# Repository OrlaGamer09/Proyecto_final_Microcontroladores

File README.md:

# Final Project Microcontrollers  
- [Spanish](./README_es.md) 

> **IMPORTANT**: This project was born from the idea of creating a Christmas-themed box, equipped with electronics, as part of the final project for the Microcontrollers course (November 2024).  

## Project Description  
The project consists of an interactive Christmas box, controlled by a **PIC16F877A** microcontroller, designed to combine creativity, electronics, and programming into a single functional device.  

## Roles and Tools Used  

### Roles  
The team is composed of:  
- **Orlando Arroyo**  
- **María López**  
- **Andrés Fábregas**  

All members participated in various roles, including:  
- Software and hardware development.  
- Product management.  

### Tools  
- **Notion**: For task assignment and progress tracking.  
- **MPLAB X IDE v5.35** and **XC8 v2.5**: For microcontroller programming.  
- **Autodesk EAGLE**: For schematic and PCB design.  

## System Operation  

Once powered on, the system displays an **initial Christmas message** on the LCD screen. From this point, the LDR sensor evaluates light conditions to determine if it is day or night, activating one of the following modes:  

### **Night Mode**  
- A decorative light is turned on.  
- A themed message is displayed on the LCD screen.  

### **Day Mode**  
In this mode, the system uses an ultrasonic sensor to detect the proximity of an object or person. If presence is detected, the following functions are activated:  
1. **Stepper motor**: Rotates a decorative figure.  
2. **Speaker**: Plays a Christmas melody.  
3. **LED strip**: Blinks in sync with the music using PWM.  
4. **LCD screen**: Displays a message related to the current activity.  

## PIC16F877A Resource Allocation  

The system utilizes the resources of the **PIC16F877A** microcontroller as follows:  

- **Port D**: Controls the LCD screen (RD0 to RD5 as outputs).  
- **Port B**: Controls the stepper motor (RB0 to RB3 as outputs).  
- **Port A**: Manages the sensors:  
  - **RA0**: Analog input for the LDR sensor.  
  - **RA1 and RA2**: Controls the ultrasonic sensor:  
    - **RA1 (Trigger)**: Output.  
    - **RA2 (Echo)**: Input.  
- **Port C**: Controls the speaker and LED strip.

## Schematic and PCB Design  

Using **Autodesk EAGLE**, we designed both the schematic and the system's PCB. These designs can be viewed in the images available in the `img` folder:  
- **Schematic**:   
- **PCB**: 

## Final Circuit of the System  

After soldering all the components onto the PCB, this is the final result of the circuit, assembled inside the box:  
- **PCB Circuit**:   

## Final Result  

After decorating the box with a Christmas style, this was the final result of the project:  
- **Photo of the Final Project**:   
- **Functionality Video**: [Watch Video](./img/resultado_final.mp4)

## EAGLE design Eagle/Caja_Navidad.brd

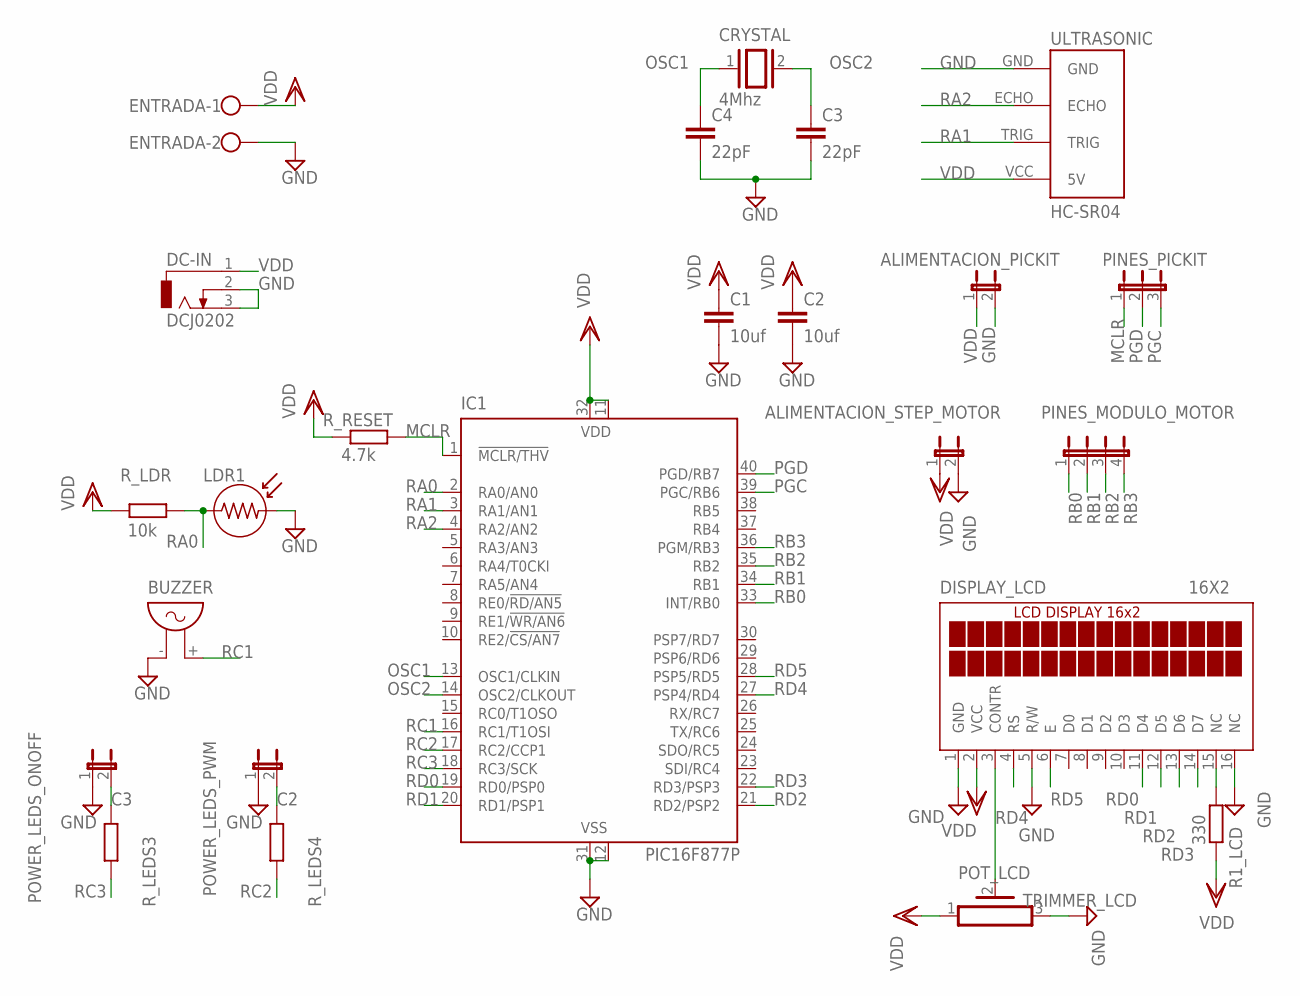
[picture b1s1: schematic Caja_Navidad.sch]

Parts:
ALIMENTACION_PICKIT: JP1E; JP1
ALIMENTACION_STEP_MOTOR: JP1E; JP1
BUZZER: F/QMX
C1, C2: 10uf; C2.5-2
C3, C4: 22pF; C2.5-2
CRYSTAL: 4Mhz; Q
DC-IN: DCJ0202
DISPLAY_LCD: 16X2; TUXGR_16X2_R2
ENTRADA: W237-102
IC1: PIC16F877P; DIL40
LDR1: LDR
PINES_MODULO_MOTOR: JP4E; JP4
PINES_PICKIT: JP2E; JP2
POWER_LEDS_ONOFF: JP1E; JP1
POWER_LEDS_PWM: JP1E; JP1
R1_LCD: 330; 0204/7
R_LDR: 10k; 0204/7
R_LEDS3: 330; 0204/7
R_LEDS4: R-EU_0204/7; 0204/7
R_RESET: 4.7k; 0204/7
TRIMMER_LCD: PV36W
ULTRASONIC: HC-SR04; HC-SR04_FOOTPRINT

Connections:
C2: POWER_LEDS_PWM.2, R_LEDS4.2
C3: POWER_LEDS_ONOFF.2, R_LEDS3.2
GND: ALIMENTACION_PICKIT.2, ALIMENTACION_STEP_MOTOR.2, BUZZER.- (1), C1.2, C2.2, C3.2, C4.2, DC-IN.2, DC-IN.3, DISPLAY_LCD.1 (GND), DISPLAY_LCD.5 (R/W), DISPLAY_LCD.16 (NC), ENTRADA.2, IC1.12 (VSS), IC1.31 (VSS), LDR1.2, POWER_LEDS_ONOFF.1, POWER_LEDS_PWM.1, TRIMMER_LCD.3, ULTRASONIC.GND
MCLR: IC1.1 (!MCLR/THV), PINES_PICKIT.1, R_RESET.2
unnamed: DISPLAY_LCD.15 (NC), R1_LCD.2
OSC1: C4.1, CRYSTAL.1, IC1.13 (OSC1/CLKIN)
OSC2: C3.1, CRYSTAL.2, IC1.14 (OSC2/CLKOUT)
PGC: IC1.39 (PGC/RB6), PINES_PICKIT.3
PGD: IC1.40 (PGD/RB7), PINES_PICKIT.2
POT_LCD: DISPLAY_LCD.3 (CONTR), TRIMMER_LCD.2
RA0: IC1.2 (RA0/AN0), LDR1.1, R_LDR.2
RA1: IC1.3 (RA1/AN1), ULTRASONIC.TRIG
RA2: IC1.4 (RA2/AN2), ULTRASONIC.ECHO
RB0: IC1.33 (INT/RB0), PINES_MODULO_MOTOR.1
RB1: IC1.34 (RB1), PINES_MODULO_MOTOR.2
RB2: IC1.35 (RB2), PINES_MODULO_MOTOR.3
RB3: IC1.36 (PGM/RB3), PINES_MODULO_MOTOR.4
RC1: BUZZER.+ (2), IC1.16 (RC1/T1OSI)
RC2: IC1.17 (RC2/CCP1), R_LEDS4.1
RC3: IC1.18 (RC3/SCK), R_LEDS3.1
RD0: DISPLAY_LCD.11 (D4), IC1.19 (RD0/PSP0)
RD1: DISPLAY_LCD.12 (D5), IC1.20 (RD1/PSP1)
RD2: DISPLAY_LCD.13 (D6), IC1.21 (RD2/PSP2)
RD3: DISPLAY_LCD.14 (D7), IC1.22 (RD3/PSP3)
RD4: DISPLAY_LCD.4 (RS), IC1.27 (PSP4/RD4)
RD5: DISPLAY_LCD.6 (E), IC1.28 (PSP5/RD5)
VDD: ALIMENTACION_PICKIT.1, ALIMENTACION_STEP_MOTOR.1, C1.1, C2.1, DC-IN.1, DISPLAY_LCD.2 (VCC), ENTRADA.1, IC1.11 (VDD), IC1.32 (VDD), R1_LCD.1, R_LDR.1, R_RESET.1, TRIMMER_LCD.1, ULTRASONIC.VCC (5V)

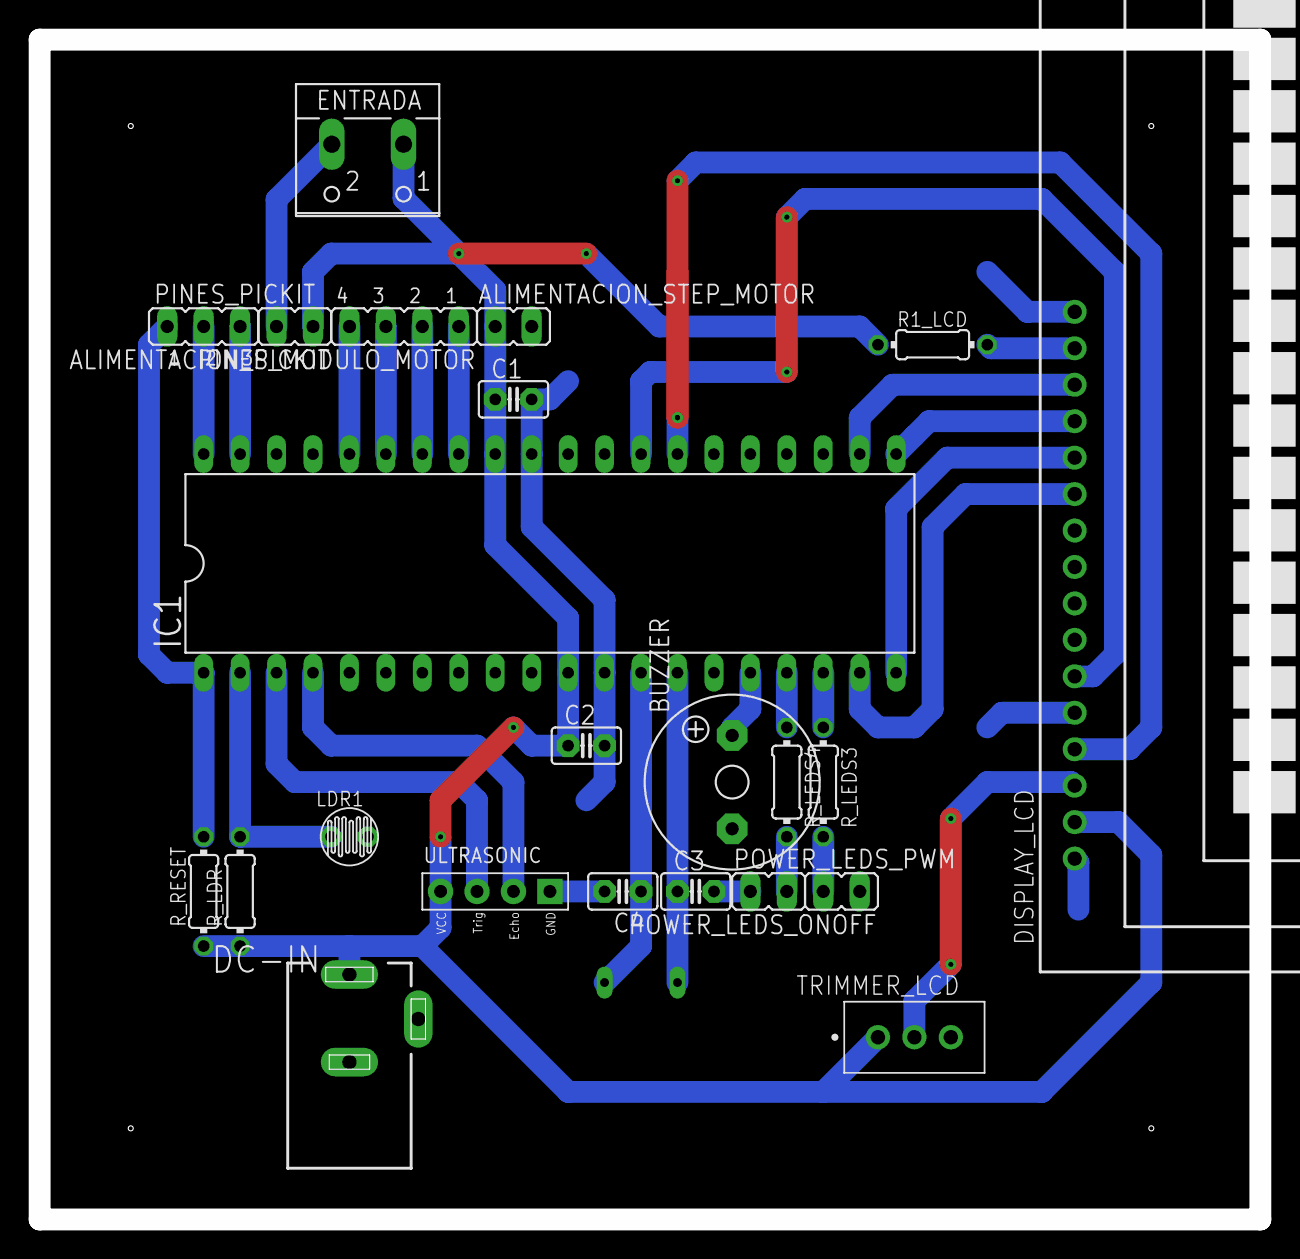
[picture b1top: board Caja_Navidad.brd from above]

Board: 2 copper layers, 85.1 x 82.2 mm, 24 parts (1 on the bottom side), 27 nets.

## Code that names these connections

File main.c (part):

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

// ULTRASONIDO:
#define Trigger RA1 // Pin de Trigger del sensor ultrasónico
#define Echo RA2 // Pin de Echo del sensor ultrasónico
int time_taken;
int distance;
int threshold_distance = 10; // Ajusta el umbral para probar diferentes distancias PULGADAS
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#define shiftLeft    0b00010000 // hace que blink el cursor
#define shiftRight   0b00010100 // hace que blink el cursor
#define lcdPort   PORTD // define el puerto al que se conecta el LCB
#define eBit  PORTDbits.RD5 // define el puerto al que se conecta E
#define rsBit  PORTDbits.RD4 // define el puerto al que se conecta RS
unsigned char lcdInfo, lcdTempInfo, rsOr; // 8 bit location for 3 variables
unsigned char n; // 8 bit location
char str[80]; //80 posiciones de memoria para enviar string a LCD
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void parpadearLEDs(void) {
    CCP1CON = 0x00;  // Configura el módulo CCP1 en modo PWM para LEDS
    for (unsigned char i = 0; i < 10; i++) {
        RC2 = 1; // Enciende LED en RC2
        RC3 = 1; // Enciende LED en RC3
        __delay_ms(400); // Retardo de 500 ms
        RC2 = 0; // Apaga LED en RC2
        RC3 = 0; // Apaga LED en RC3
        __delay_ms(400); // Retardo de 500 ms
    }
}
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    PORTD=0x00;
    PORTE=0x00;
    
    TRISA=0xFD; // Configura todos los pines de PORTA como entradas excepto RA1
    TRISB=0x00; // Todo salidas
    TRISC=0x00; // Todo salidas
    TRISD=0x00; // Todo salidas
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
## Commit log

2024-11-25 add media
2024-11-25 add Eagle Files
2024-11-25 add Eagle Files v2
